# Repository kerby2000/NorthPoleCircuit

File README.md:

# North Pole BLE Audio Card

This is a work-in-progress derivative of the original
[Janky Jingle Crew NorthPoleCircuit](https://github.com/Janky-Jingle-Crew/NorthPoleCircuit).

The goal is to turn the original moving magnetic Christmas PCB card into a BLE-enabled audio postcard / mini-diorama with rechargeable battery power, real audio playback, capacitive touch controls, Hall checkpoints, and addressable RGB lighting.

## Status

Current state: hardware revision in progress.

- KiCad 10 PCB project is included under `PCB/`.
- Draft JLCPCB manufacturing files are included under `PCB/production/`.
- Firmware bring-up scaffold lives under `Firmware/northpole_ch592_bringup/` and is based on the WCH CH592 EVT BLE Peripheral project.
- The board has not yet been validated on real hardware.
- The audio playback IC sourcing is still a risk and should be checked before ordering.

Do not treat the current production files as a proven release. Review ERC/DRC, BOM sourcing, assembly rotations, antenna keepout, LiPo safety, and audio availability before manufacturing.

## Repository Layout

```text
PCB/                     KiCad 10 hardware project and draft manufacturing files
Firmware/                CH592X BLE/audio firmware bring-up project and docs
audio_assets/            WT2003 external-flash manifest and copy-order packer
Code/                    Original upstream firmware, kept for reference only
CAD/                     Original upstream mechanical assets
Media/                   Original media plus new PCB renders
CHANGES_FROM_ORIGINAL.md Summary of the redesign
```

## Hardware Overview

This redesign keeps the magnetic track idea from the original project, but changes most of the control electronics.

Main blocks in the current KiCad design:

- CH592X BLE MCU
- 3 x DRV8837 H-bridge motor drivers
- WT2003H4-24SS audio playback IC
- PY25Q64HA SPI NOR flash for audio assets
- IP5209 1S LiPo charge / boost PMIC
- ME6211 3.3 V regulator
- 2 x DRV5032 Hall sensors
- 4 capacitive touch buttons
- 6 x 1010 addressable RGB LEDs, currently JLCPCB `C41347988`
- USB-C input
- 32 MHz crystal
- WCH-style PCB BLE antenna footprint
- J3 WCH-LinkE/debug Tag-Connect footprint
- J4 WT2003 USB update Tag-Connect footprint
- thin speaker and 1S LiPo battery placement helpers

## Opening The PCB

Use KiCad 10.

Open:

```text
PCB/NorthPoleCircuit_PCB.kicad_pro
```

The local custom libraries are kept in the repo:

- `PCB/cust_sym.kicad_sym`
- `PCB/cust_fp/`
- `PCB/footprints.pretty/`

## Manufacturing Files

Draft manufacturing outputs are in:

```text
PCB/production/
```

Included files:

- `NorthPoleCircuit_PCB14.zip` - Gerber/drill archive
- `bom.csv` - JLCPCB BOM
- `positions.csv` - JLCPCB pick-and-place
- `designators.csv` - Fabrication Toolkit designator output

Before ordering, re-export these from KiCad/Fabrication Toolkit and compare against the files here.

## Firmware

Firmware for this revision is under [Firmware/](./Firmware/). The initial target is `Firmware/northpole_ch592_bringup/`, copied from a working WCH CH592 EVT BLE Peripheral example and then modified at the application layer.

Important hardware notes:

- J3 is WCH-LinkE/debug: 1=3.3V target reference, 2=TIO/SWDIO/PB14, 4=TCK/SWDCK/PB15, 5=GND, 3/6=NC.
- PB14/PB15 are shared with IP5209 I2C through R15/R14 0 ohm links. Do not expect IP5209 I2C access during active WCH-LinkE debugging.
- J4 is intended as WT2003 USB update only, not ARM SWD, but the current PCB revision is blocked for update use: pin 1 is unconnected, so J4 has D+/D-/GND only. Do not use it for WT2003 USB update until +5 V is routed or a rework power path is documented.
- PB0 controls global DRV8837 `~SLEEP`; idle/fault state is `/SLEEP` low and all bridge IN pins low.

The existing `Code/` directory is from the original upstream NorthPoleCircuit project and is not firmware for the CH592X BLE/audio redesign.

## Major Changes

See [CHANGES_FROM_ORIGINAL.md](./CHANGES_FROM_ORIGINAL.md).

Short version:

- single BLE-capable CH592X control architecture
- rechargeable LiPo power path
- audio playback IC and speaker path
- capacitive touch buttons
- Hall checkpoint sensing
- addressable RGB LEDs
- revised KiCad 10 PCB with custom artwork and JLCPCB metadata

## Attribution

Original project:

- [Janky Jingle Crew - NorthPoleCircuit](https://github.com/Janky-Jingle-Crew/NorthPoleCircuit)

Related inspiration:

- [Jeff McBride - Gauss Speedway](https://jeffmcbride.net/gauss-speedway/)

This repository is a derivative redesign. The original concept, mechanical idea, and much of the visual/magnetic-track inspiration belong to the original authors.

## License

TODO.

Before publishing a release or manufacturing publicly, verify the license/permission status of the upstream NorthPoleCircuit project. If the upstream project has no explicit open-source license, only the new original work in this redesign can be licensed without additional permission.

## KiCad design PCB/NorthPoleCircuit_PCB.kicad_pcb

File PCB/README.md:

# PCB

This folder contains the KiCad 10 hardware project for the BLE/audio redesign.

Open `NorthPoleCircuit_PCB.kicad_pro` in KiCad 10.

Local project assets:

- `cust_sym.kicad_sym` - custom symbols
- `cust_fp/` - custom footprints used by the board
- `footprints.pretty/` - local STEP models referenced by the PCB
- `production/` - draft manufacturing outputs

The production files are draft outputs for review. Re-export them from KiCad/Fabrication Toolkit before ordering boards.

## Firmware And Bring-Up

The detailed CH592X firmware implementation and first-board bring-up plan is maintained in `../Firmware/README.md`.

Use the bring-up/test firmware profile first. It should keep all high-power outputs disabled at boot and expose explicit diagnostic hooks for power, touch, RGB LEDs, Hall sensors, audio, BLE, and DRV8837 motor testing before running the production firmware.

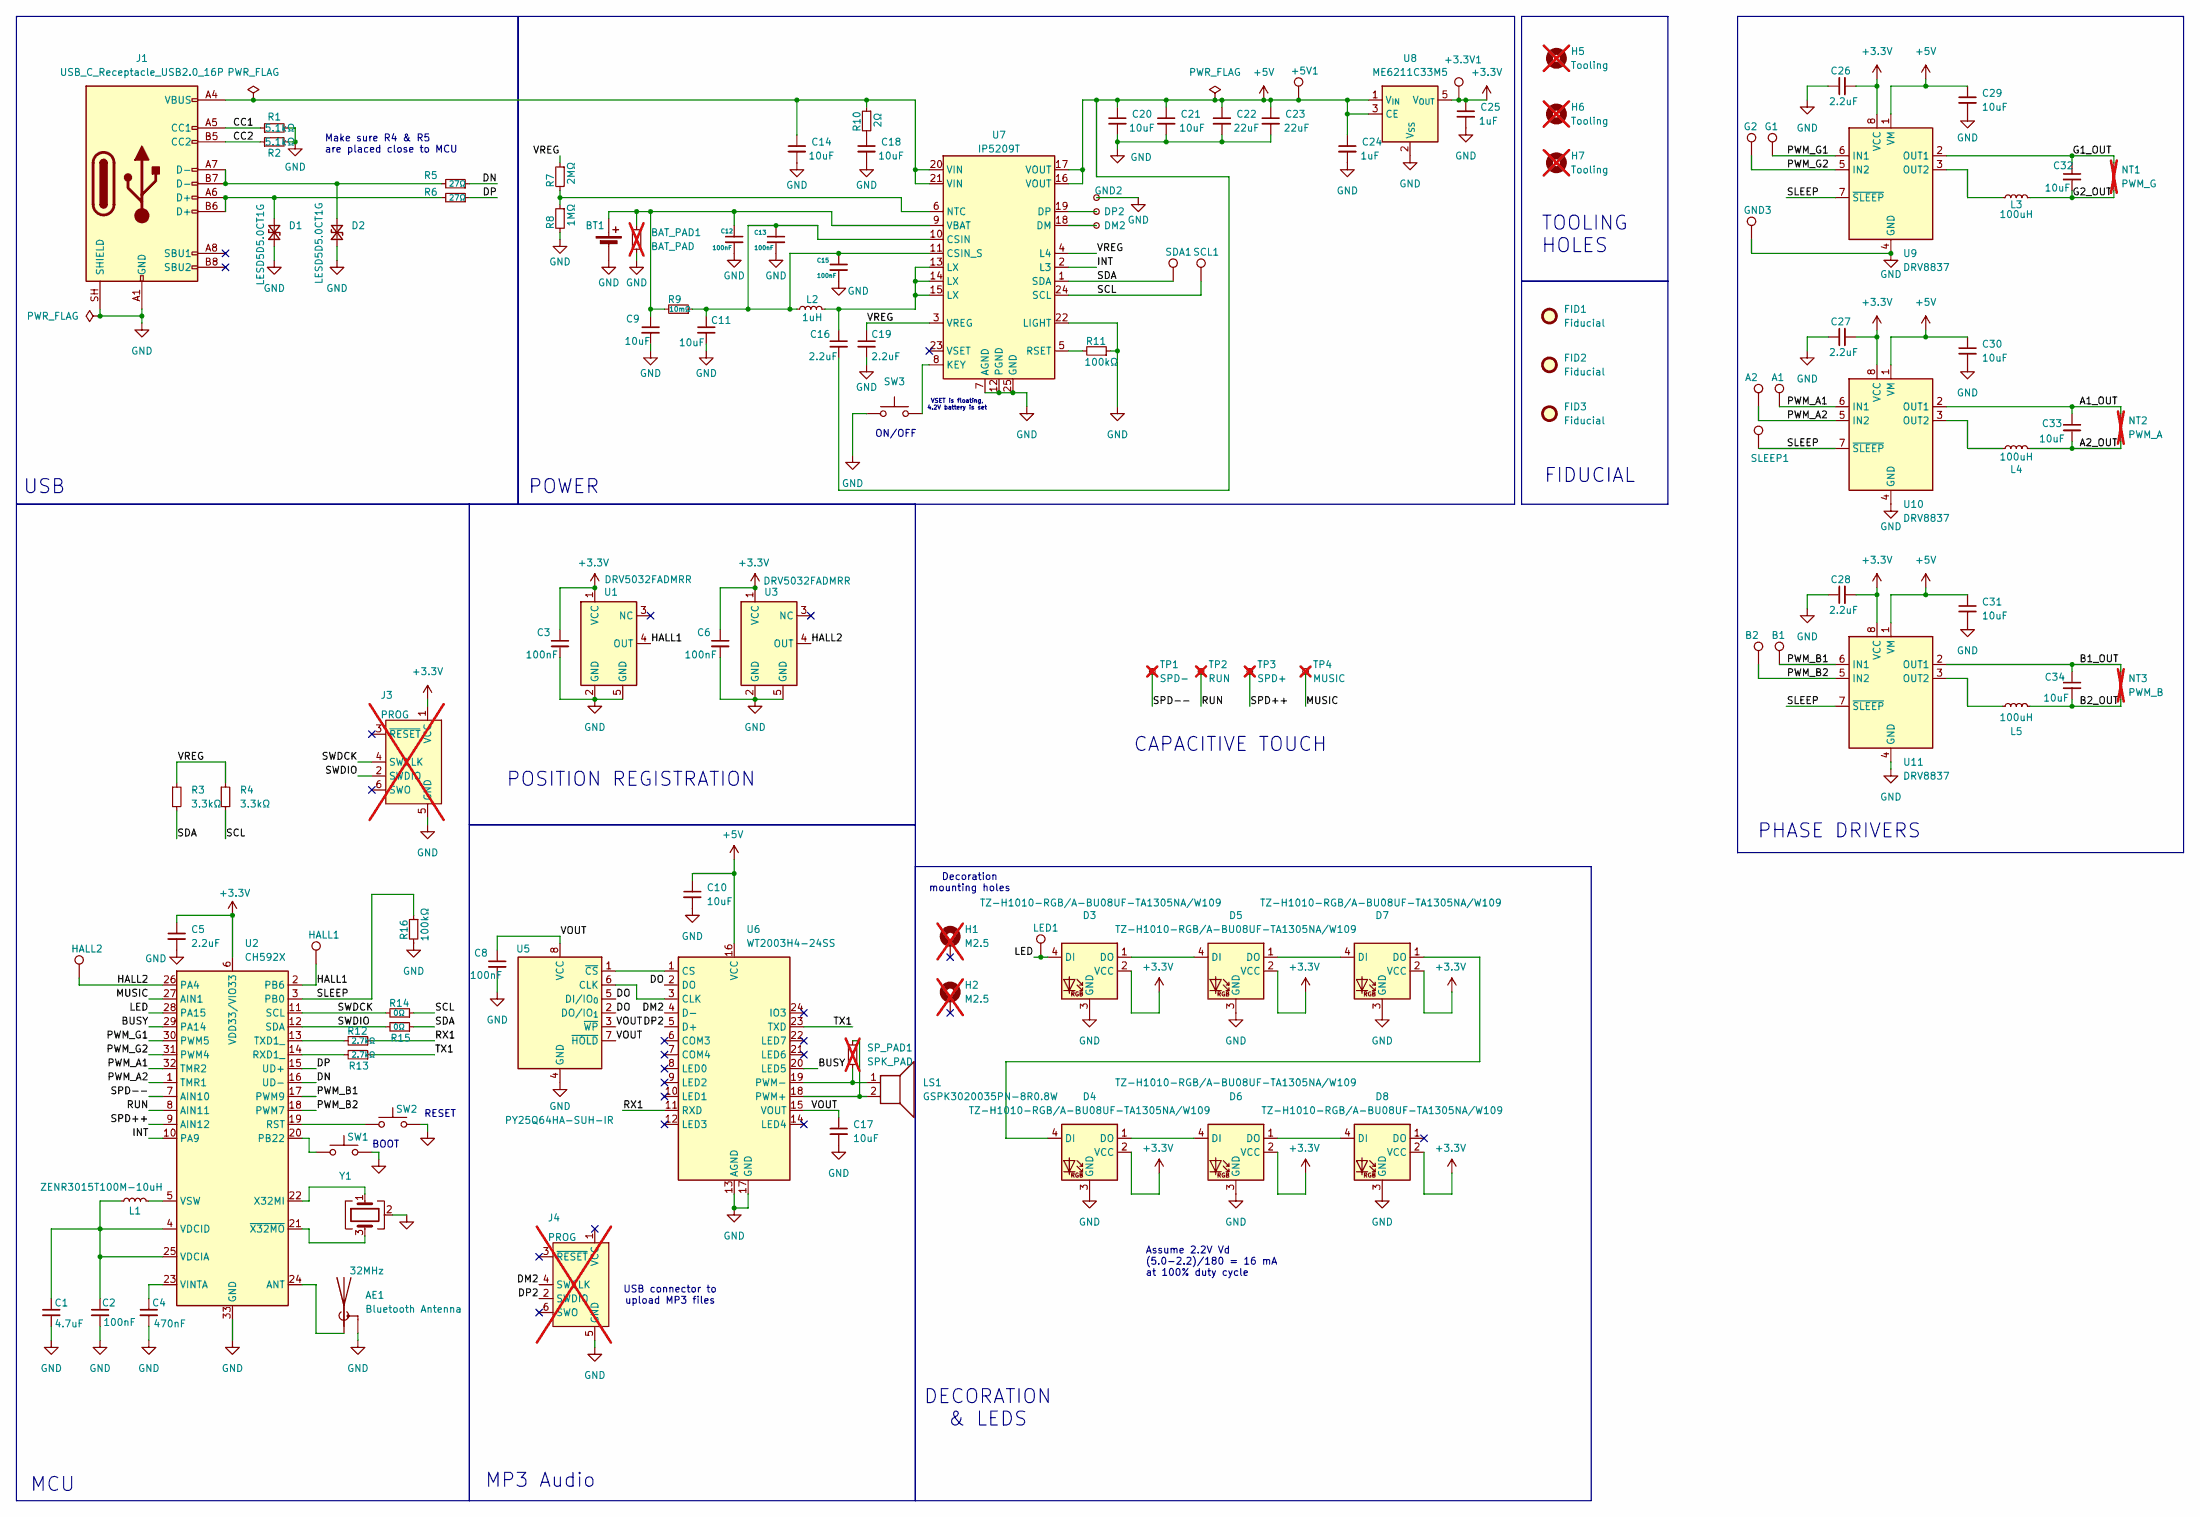
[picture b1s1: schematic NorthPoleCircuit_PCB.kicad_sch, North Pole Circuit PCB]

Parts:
+3.3V1: +3.3V; TestPoint_Pad_D1.5mm
+5V1: +5V; TestPoint_Pad_D1.5mm
A1: A1; TestPoint_Pad_D1.5mm
A2: A2; TestPoint_Pad_D1.5mm
AE1: Bluetooth Antenna; WCH_ANT_F_1_2_4G_1p0mmFR4_12p3x5p6
B1: B1; TestPoint_Pad_D1.5mm
B2: B2; TestPoint_Pad_D1.5mm
BAT_PAD1: BAT_PAD; Battery_LiPo_500mAh_30x35x4mm_WirePads; not fitted
BT1: LiPo_1S_500mAh; Battery_LiPo_500mAh_30x35x4mm_Body
C1: 4.7uF; C_1206_3216Metric; MPN CL31B475KAHNNNE; JLCPCB C1872
C2, C3, C6, C8, C12, C13, C15: 100nF; C_0402_1005Metric; MPN CL05B104KO5NNNC; JLCPCB C1525
C4: 470nF; C_1206_3216Metric; MPN CL31B474KBHNNNE; JLCPCB C71084
C5, C16, C19, C26, C27, C28: 2.2uF; C_1206_3216Metric; MPN CL31B225KBHNNNE; JLCPCB C50254
C9, C10, C11, C14, C17, C18, C20, C21, C29, C30, C31, C32, C33, C34: 10uF; C_1206_3216Metric; MPN CL31A106KBHNNNE; JLCPCB C13585
C22, C23: 22uF; C_1206_3216Metric; MPN CL31A226KAHNNNE; JLCPCB C12891
C24, C25: 1uF; C_1206_3216Metric; MPN CL31B105KBHNNNE; JLCPCB C1848
D1, D2: LESD5D5.0CT1G; D_SOD-523; MPN LESD5D5.0CT1G(UMW); JLCPCB C5199850
D3, D4, D5, D6, D7, D8: TZ-H1010-RGB/A-BU08UF-TA1305NA/W109; ws2812b_1010; MPN TZ-H1010-RGB/A-BU08UF-TA1305NA/W109; JLCPCB C41347988
DM2: TestPoint_Small; TestPoint_Pad_D1.0mm
DP2: TestPoint_Small; TestPoint_Pad_D1.0mm
FID1, FID2, FID3: Fiducial; Fiducial_0.75mm_Mask1.5mm
G1: G1; TestPoint_Pad_D1.5mm
G2: G2; TestPoint_Pad_D1.5mm
GND2: TestPoint_Small; TestPoint_Pad_D1.0mm
GND3: HALL2; TestPoint_Pad_D1.5mm
H1, H2: M2.5; MountingHole_2.7mm_M2.5_DIN965_Pad; not fitted
H5, H6, H7: Tooling; tooling_hole; not fitted
HALL1: HALL1; TestPoint_Pad_D1.5mm
HALL2: HALL2; TestPoint_Pad_D1.5mm
J1: USB_C_Receptacle_USB2.0_16P; USB_C_Receptacle_HRO_TYPE-C-31-M-12; MPN TYPE-C-31-M-12; JLCPCB C165948
J3, J4: PROG; Tag-Connect_TC2030-IDC-NL_2x03_P1.27mm_Vertical; not fitted
L1: ZENR3015T100M-10uH; L_Taiyo-Yuden_NR-30xx; MPN ZENR3015T100M-10uH; JLCPCB C42427989
L2: 1uH; L_Wuerth_HCI-7030; MPN MAPM0630F-1R0M-LF; JLCPCB C280920
L3, L4, L5: 100uH; SMMS0650-101M; MPN SMMS0650-101M; JLCPCB C2894722
LED1: LED; TestPoint_Pad_D1.5mm
LS1: GSPK3020035PN-8R0.8W
NT1: PWM_G; NetTie_1.25mm; not fitted
NT2: PWM_A; NetTie_1.25mm; not fitted
NT3: PWM_B; NetTie_1.25mm; not fitted
R1, R2: 5.1kΩ; R_0402_1005Metric; MPN 0402WGF5101TCE; JLCPCB C25905
R3, R4: 3.3kΩ; R_0402_1005Metric; MPN 0402WGF3301TCE; JLCPCB PN C25890
R5, R6: 27Ω; R_0402_1005Metric; MPN 0402WGF270JTCE; JLCPCB C25100
R7: 2MΩ; R_0805_2012Metric; MPN 0805W8J0205T5E; JLCPCB C40088
R8: 1MΩ; R_0402_1005Metric; MPN 0402WGF1004TCE; JLCPCB C26083
R9: 10mΩ; R_1206_3216Metric; MPN FRM121WFR010TM; JLCPCB C7467248
R10: 2Ω; R_0402_1005Metric; MPN 0402WGJ020JTCE; JLCPCB C25157
R11, R16: 100kΩ; R_0402_1005Metric; MPN 0402WGF1003TCE; JLCPCB C25741
R12, R13: 2.7kΩ; R_0402_1005Metric; MFR.Part # 0402WGF2701TCE; LCSC Part C25885
R14, R15: 0Ω; R_0402_1005Metric; MFR.Part # 0402WGF0000TCE; LCSC Part C17168
SCL1: SCL; TestPoint_Pad_D1.5mm
SDA1: SDA; TestPoint_Pad_D1.5mm
SLEEP1: SLEEP; TestPoint_Pad_D1.5mm
SP_PAD1: SPK_PAD; Speaker_GSPK3020035PN_WirePads; not fitted
SW1, SW2: TS-1088-AR02016; SW_Push_SPST_NO_Alps_SKRK; MPN TS-1088-AR02016; JLCPCB C720477
SW3: TS-1187A-C-E-B; SW_SPST_SKQG_WithStem; MPN TS-1187A-C-E-B; JLCPCB C318887
TP1: SPD-; Cap_Touch_10mm; not fitted
TP2: RUN; Cap_Touch_10mm; not fitted
TP3: SPD+; Cap_Touch_10mm; not fitted
TP4: MUSIC; Cap_Touch_10mm; not fitted
U1, U3: DRV5032FADMRR; Texas_X2SON-4-1EP_1.1x1.4mm_P0.5mm_EP0.8x0.6mm; MPN DRV5032FADMRR; JLCPCB C2152496
U2: CH592X; QFN-32-1EP_4x4mm_P0.4mm_EP2.65x2.65mm; MPN CH592X; JLCPCB C42442063
U5: PY25Q64HA-SUH-IR; SOIC-8_5.3x5.3mm_P1.27mm; MPN PY25Q64HA-SUH-IR; JLCPCB C22438999
U6: WT2003H4-24SS; SSOP-24_3.9x8.7mm_P0.635mm; MPN WT2003H4-24SS; JLCPCB C2931181
U7: IP5209T; QFN-24-1EP_4x4mm_P0.5mm_EP2.5x2.5mm; MPN IP5209T; JLCPCB C284964
U8: ME6211C33M5; SOT-23-5; MPN ME6211C33M5G-N; JLCPCB C82942
U9, U10, U11: DRV8837; WSON-8-1EP_2x2mm_P0.5mm_EP0.9x1.6mm; MPN DRV8837DSGR; JLCPCB C39159
Y1: 32MHz; Crystal_SMD_3225-4Pin_3.2x2.5mm; MPN X322532MOB4SI; LCSC Part C9009

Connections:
+3.3V: +3.3V1.1 (1_1), C3.1, C5.1, C6.1, C25.1, C26.2, C27.2, C28.2, D3.2 (VCC), D4.2 (VCC), D5.2 (VCC), D6.2 (VCC), D7.2 (VCC), D8.2 (VCC), J3.1 (VCC), U1.1 (VCC), U2.6 (VDD33/VIO33), U3.1 (VCC), U8.5 (V_{OUT}), U9.8 (VCC), U10.8 (VCC), U11.8 (VCC)
+5V: +5V1.1 (1_1), C10.1, C16.2, C20.1, C21.1, C22.1, C23.1, C24.1, C29.1, C30.1, C31.1, U6.16 (VCC), U7.16 (VOUT), U7.17 (VOUT), U8.1 (V_{IN}), U8.3 (CE), U9.1 (VM), U10.1 (VM), U11.1 (VM)
/A1_OUT: C33.1, NT2.2, U10.2 (OUT1)
/A2_OUT: C33.2, L4.2, NT2.1
/B1_OUT: C34.1, NT3.2, U11.2 (OUT1)
/B2_OUT: C34.2, L5.2, NT3.1
/BUSY: U2.29 (PA14), U6.20 (LED5)
/CC1: J1.A5 (CC1), R1.1
/CC2: J1.B5 (CC2), R2.1
/DM2: J4.4 (SWCLK), U6.4 (D-)
/DN: R5.1, U2.16 (UD-)
/DO: U5.2 (DO/IO_{1}), U5.5 (DI/IO_{0}), U6.2 (DO)
/DP: R6.1, U2.15 (UD+)
/DP2: J4.2 (SWDIO), U6.5 (D+)
/G1_OUT: C32.1, NT1.2, U9.2 (OUT1)
/G2_OUT: C32.2, L3.2, NT1.1
/INT: U2.10 (PA9), U7.2 (L3)
/LED: D3.4 (DI), LED1.1 (1_1), U2.28 (PA15)
/MUSIC: TP4.1 (1_1), U2.27 (AIN1)
/PWM_A1: A1.1 (1_1), U2.32 (TMR2), U10.6 (IN1)
/PWM_A2: A2.1 (1_1), U2.1 (TMR1), U10.5 (IN2)
/PWM_B1: B1.1 (1_1), U2.17 (PWM9), U11.6 (IN1)
/PWM_B2: B2.1 (1_1), U2.18 (PWM7), U11.5 (IN2)
/PWM_G1: G1.1 (1_1), U2.30 (PWM5), U9.6 (IN1)
/PWM_G2: G2.1 (1_1), U2.31 (PWM4), U9.5 (IN2)
/RUN: TP2.1 (1_1), U2.8 (AIN11)
/RX1: R12.1, U6.11 (RXD)
/SCL: R4.2, R14.1, SCL1.1 (1_1), U7.24 (SCL)
/SDA: R3.2, R15.1, SDA1.1 (1_1), U7.1 (SDA)
/SLEEP: R16.1, SLEEP1.1 (1_1), U2.3 (PB0), U9.7 (~SLEEP), U10.7 (~SLEEP), U11.7 (~SLEEP)
/SPD++: TP3.1 (1_1), U2.9 (AIN12)
/SPD--: TP1.1 (1_1), U2.7 (AIN10)
/SWDCK: J3.4 (SWCLK), R14.2, U2.11 (SCL)
/SWDIO: J3.2 (SWDIO), R15.2, U2.12 (SDA)
/TX1: R13.1, U6.23 (TXD)
/VOUT: C8.1, C17.1, U5.3 (~WP), U5.7 (~HOLD), U5.8 (VCC), U6.15 (VOUT)
/VREG: C19.1, R3.1, R4.1, R7.1, U7.3 (VREG), U7.4 (L4)
unnamed: AE1.1 (A), U2.24 (ANT)
unnamed: C14.1, J1.A4 (VBUS), J1.A9 (VBUS), J1.B4 (VBUS), J1.B9 (VBUS), R10.1, U7.20 (VIN), U7.21 (VIN)
unnamed: C16.1, L2.2, U7.13 (LX), U7.14 (LX), U7.15 (LX)
unnamed: C18.1, R10.2
unnamed: D1.2 (A2), J1.A6 (D+), J1.B6 (D+), R6.2
unnamed: D2.2 (A2), J1.A7 (D-), J1.B7 (D-), R5.2
unnamed: D3.1 (DO), D5.4 (DI)
unnamed: D4.4 (DI), D7.1 (DO)
unnamed: D4.1 (DO), D6.4 (DI)
unnamed: D5.1 (DO), D7.4 (DI)
unnamed: D6.1 (DO), D8.4 (DI)
unnamed: R13.2, U2.14 (RXD1_)
unnamed: R12.2, U2.13 (TXD1_)
unnamed: SW1.1, U2.20 (PB22)
unnamed: SW2.1, U2.19 (RST)
unnamed: C1.1, C2.1, L1.1, U2.4 (VDCID), U2.25 (VDCIA)
unnamed: C4.1, U2.23 (VINTA)
unnamed: L1.2, U2.5 (VSW)
unnamed: U2.22 (X32MI), Y1.1
unnamed: U2.21 (~X32MO), Y1.3
unnamed: U5.6 (CLK), U6.3 (CLK)
unnamed: U5.1 (~CS), U6.1 (CS)
unnamed: LS1.2, SP_PAD1.1, U6.18 (PWM+)
unnamed: LS1.1, SP_PAD1.2, U6.19 (PWM-)
unnamed: C11.1, C13.1, C15.1, L2.1, R9.1, U7.10 (CSIN), U7.11 (CSIN_S)
unnamed: DM2.1 (1_1), U7.18 (DM)
unnamed: DP2.1 (1_1), U7.19 (DP)
unnamed: SW3.2, U7.8 (KEY)
unnamed: R7.2, R8.1, U7.6 (NTC)
unnamed: R11.2, U7.5 (RSET)
unnamed: BAT_PAD1.1, BT1.1 (+), C9.1, C12.1, R9.2, U7.9 (VBAT)
unnamed: L3.1, U9.3 (OUT2)
unnamed: L4.1, U10.3 (OUT2)
unnamed: L5.1, U11.3 (OUT2)

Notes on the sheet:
MCU
RESET
DECORATION & LEDS
USB
POWER
FIDUCIAL
CAPACITIVE TOUCH
USB connector to upload MP3 files
POSITION REGISTRATION
ON/OFF
Decoration mounting holes
TOOLING HOLES
MP3 Audio
Assume 2.2V Vd (5.0-2.2)/180 = 16 mA at 100% duty cycle
Make sure R4 & R5 are placed close to MCU
BOOT
PHASE DRIVERS
VSET is floating, 4.2V battery is set

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
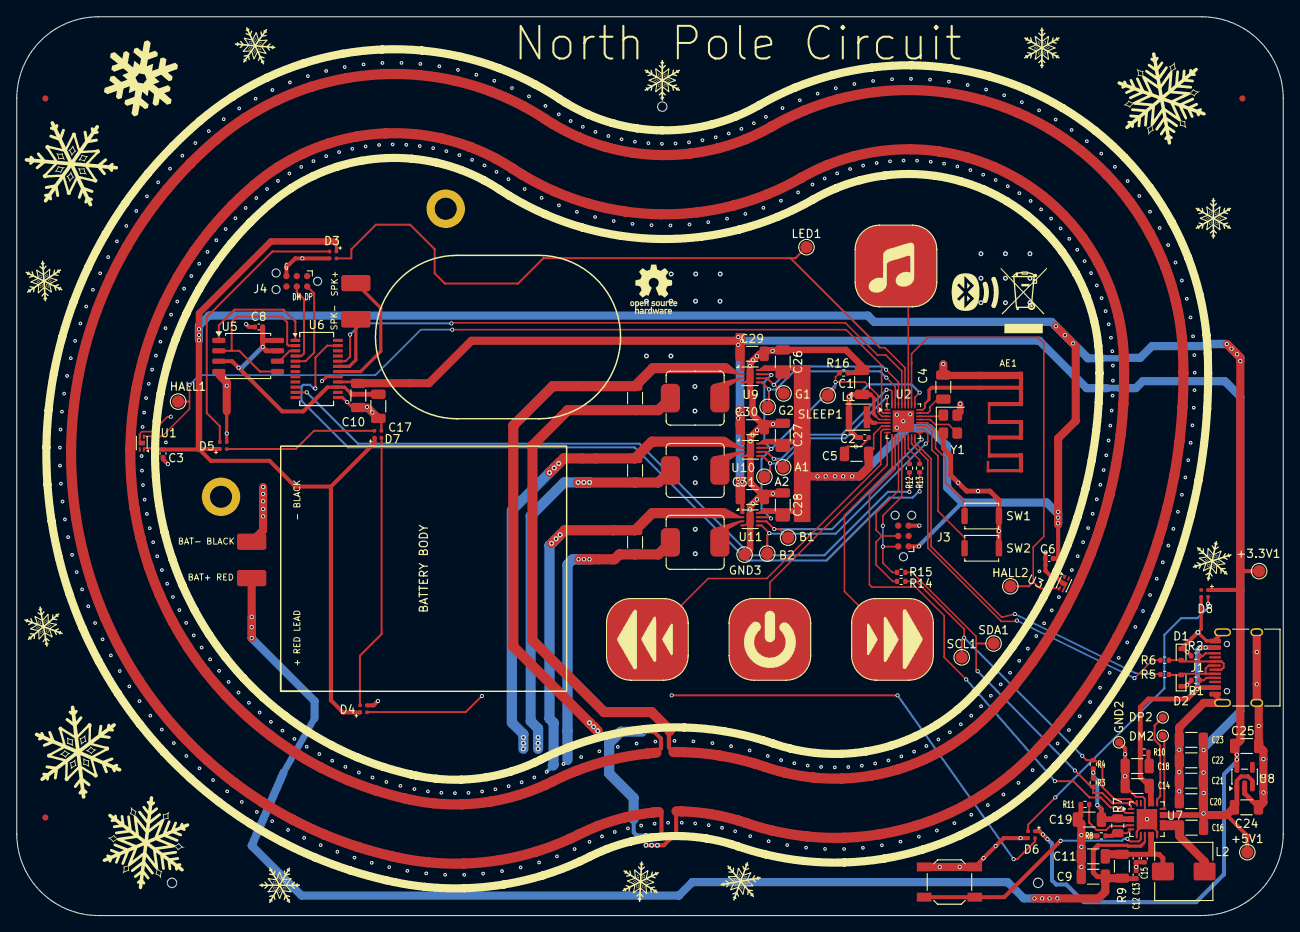
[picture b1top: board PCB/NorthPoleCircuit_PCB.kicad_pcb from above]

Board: 4 copper layers, 155.0 x 110.0 mm, 117 parts (0 on the bottom side), 74 nets.

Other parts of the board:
BT1_BODY: LiPo_1S_500mAh; Battery_LiPo_500mAh_30x35x4mm_Body
LS1_BODY: GSPK3020035PN-8R0.8W; Speaker_GSPK3020035PN_Body

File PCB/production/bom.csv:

Designator,Footprint,Quantity,Value,LCSC Part #,JLCPCB Part #,JLCPCB,MPN,MFR.Part #
C1,1206,1,4.7uF,C1872,C1872,C1872,CL31B475KAHNNNE,
"C10, C11, C14, C17, C18, C20, C21, C29, C30, C31, C32, C33, C34, C9",1206,14,10uF,C13585,C13585,C13585,CL31A106KBHNNNE,
"C12, C13, C15, C2, C3, C6, C8",0402,7,100nF,C1525,C1525,C1525,CL05B104KO5NNNC,
"C16, C19, C26, C27, C28, C5",1206,6,2.2uF,C50254,C50254,C50254,CL31B225KBHNNNE,
"C22, C23",1206,2,22uF,C12891,C12891,C12891,CL31A226KAHNNNE,
"C24, C25",1206,2,1uF,C1848,C1848,C1848,CL31B105KBHNNNE,
C4,1206,1,470nF,C71084,C71084,C71084,CL31B474KBHNNNE,
"D1, D2",D_SOD-523,2,LESD5D5.0CT1G,C5199850,C5199850,C5199850,LESD5D5.0CT1G(UMW),
"D3, D4, D5, D6, D7, D8",ws2812b_1010,6,TZ-H1010-RGB/A-BU08UF-TA1305NA/W109,C41347988,C41347988,C41347988,TZ-H1010-RGB/A-BU08UF-TA1305NA/W109,TZ-H1010-RGB/A-BU08UF-TA1305NA/W109
J1,USB_C_Receptacle_HRO_TYPE-C-31-M-12,1,USB_C_Receptacle_USB2.0_16P,C165948,C165948,C165948,TYPE-C-31-M-12,
L1,L_Taiyo-Yuden_NR-30xx,1,ZENR3015T100M-10uH,C42427989,C42427989,C42427989,ZENR3015T100M-10uH,
L2,L_Wuerth_HCI-7030,1,1uH,C280920,C280920,C280920,MAPM0630F-1R0M-LF,
"L3, L4, L5",SMMS0650-101M,3,100uH,C2894722,C2894722,C2894722,SMMS0650-101M,
"R1, R2",0402,2,5.1kΩ,C25905,C25905,C25905,0402WGF5101TCE,
R10,0402,1,2Ω,C25157,C25157,C25157,0402WGJ020JTCE,
R11,0402,1,100kΩ,C25741,C25741,C25741,0402WGF1003TCE,
"R12, R13",0402,2,2.7kΩ,C25885,C25885,C25885,0402WGF2701TCE,0402WGF2701TCE
"R3, R4",0402,2,3.3kΩ,C25890,C25890,C25890,0402WGF3301TCE,
"R5, R6",0402,2,27Ω,C25100,C25100,C25100,0402WGF270JTCE,
R7,0805,1,2MΩ,C40088,C40088,C40088,0805W8J0205T5E,
R8,0402,1,1MΩ,C26083,C26083,C26083,0402WGF1004TCE,
R9,1206,1,10mΩ,C7467248,C7467248,C7467248,FRM121WFR010TM,
"SW1, SW2",SW_Push_SPST_NO_Alps_SKRK,2,TS-1088-AR02016,C720477,C720477,C720477,TS-1088-AR02016,
SW3,SW_SPST_SKQG_WithStem,1,TS-1187A-C-E-B,C318887,C318887,C318887,TS-1187A-C-E-B,
"U1, U3",Texas_X2SON-4-1EP_1.1x1.4mm_P0.5mm_EP0.8x0.6mm,2,DRV5032FADMRR,C2152496,C2152496,C2152496,DRV5032FADMRR,
"U10, U11, U9",WSON-8-1EP_2x2mm_P0.5mm_EP0.9x1.6mm,3,DRV8837,C39159,C39159,C39159,DRV8837DSGR,
U2,QFN-32-1EP_4x4mm_P0.4mm_EP2.65x2.65mm,1,CH592X,C42442063,C42442063,C42442063,CH592X,
U5,SOIC-8_5.3x5.3mm_P1.27mm,1,PY25Q64HA-SUH-IR,C22438999,C22438999,C22438999,PY25Q64HA-SUH-IR,
U6,SSOP-24_3.9x8.7mm_P0.635mm,1,WT2003H4-24SS,C2931181,C2931181,C2931181,WT2003H4-24SS,
U7,QFN-24-1EP_4x4mm_P0.5mm_EP2.5x2.5mm,1,IP5209T,C284964,C284964,C284964,IP5209T,
U8,SOT-23-5,1,ME6211C33M5,C82942,C82942,C82942,ME6211C33M5G-N,
Y1,Crystal_SMD_3225-4Pin_3.2x2.5mm,1,32MHz,C9009,C9009,C9009,X322532MOB4SI,

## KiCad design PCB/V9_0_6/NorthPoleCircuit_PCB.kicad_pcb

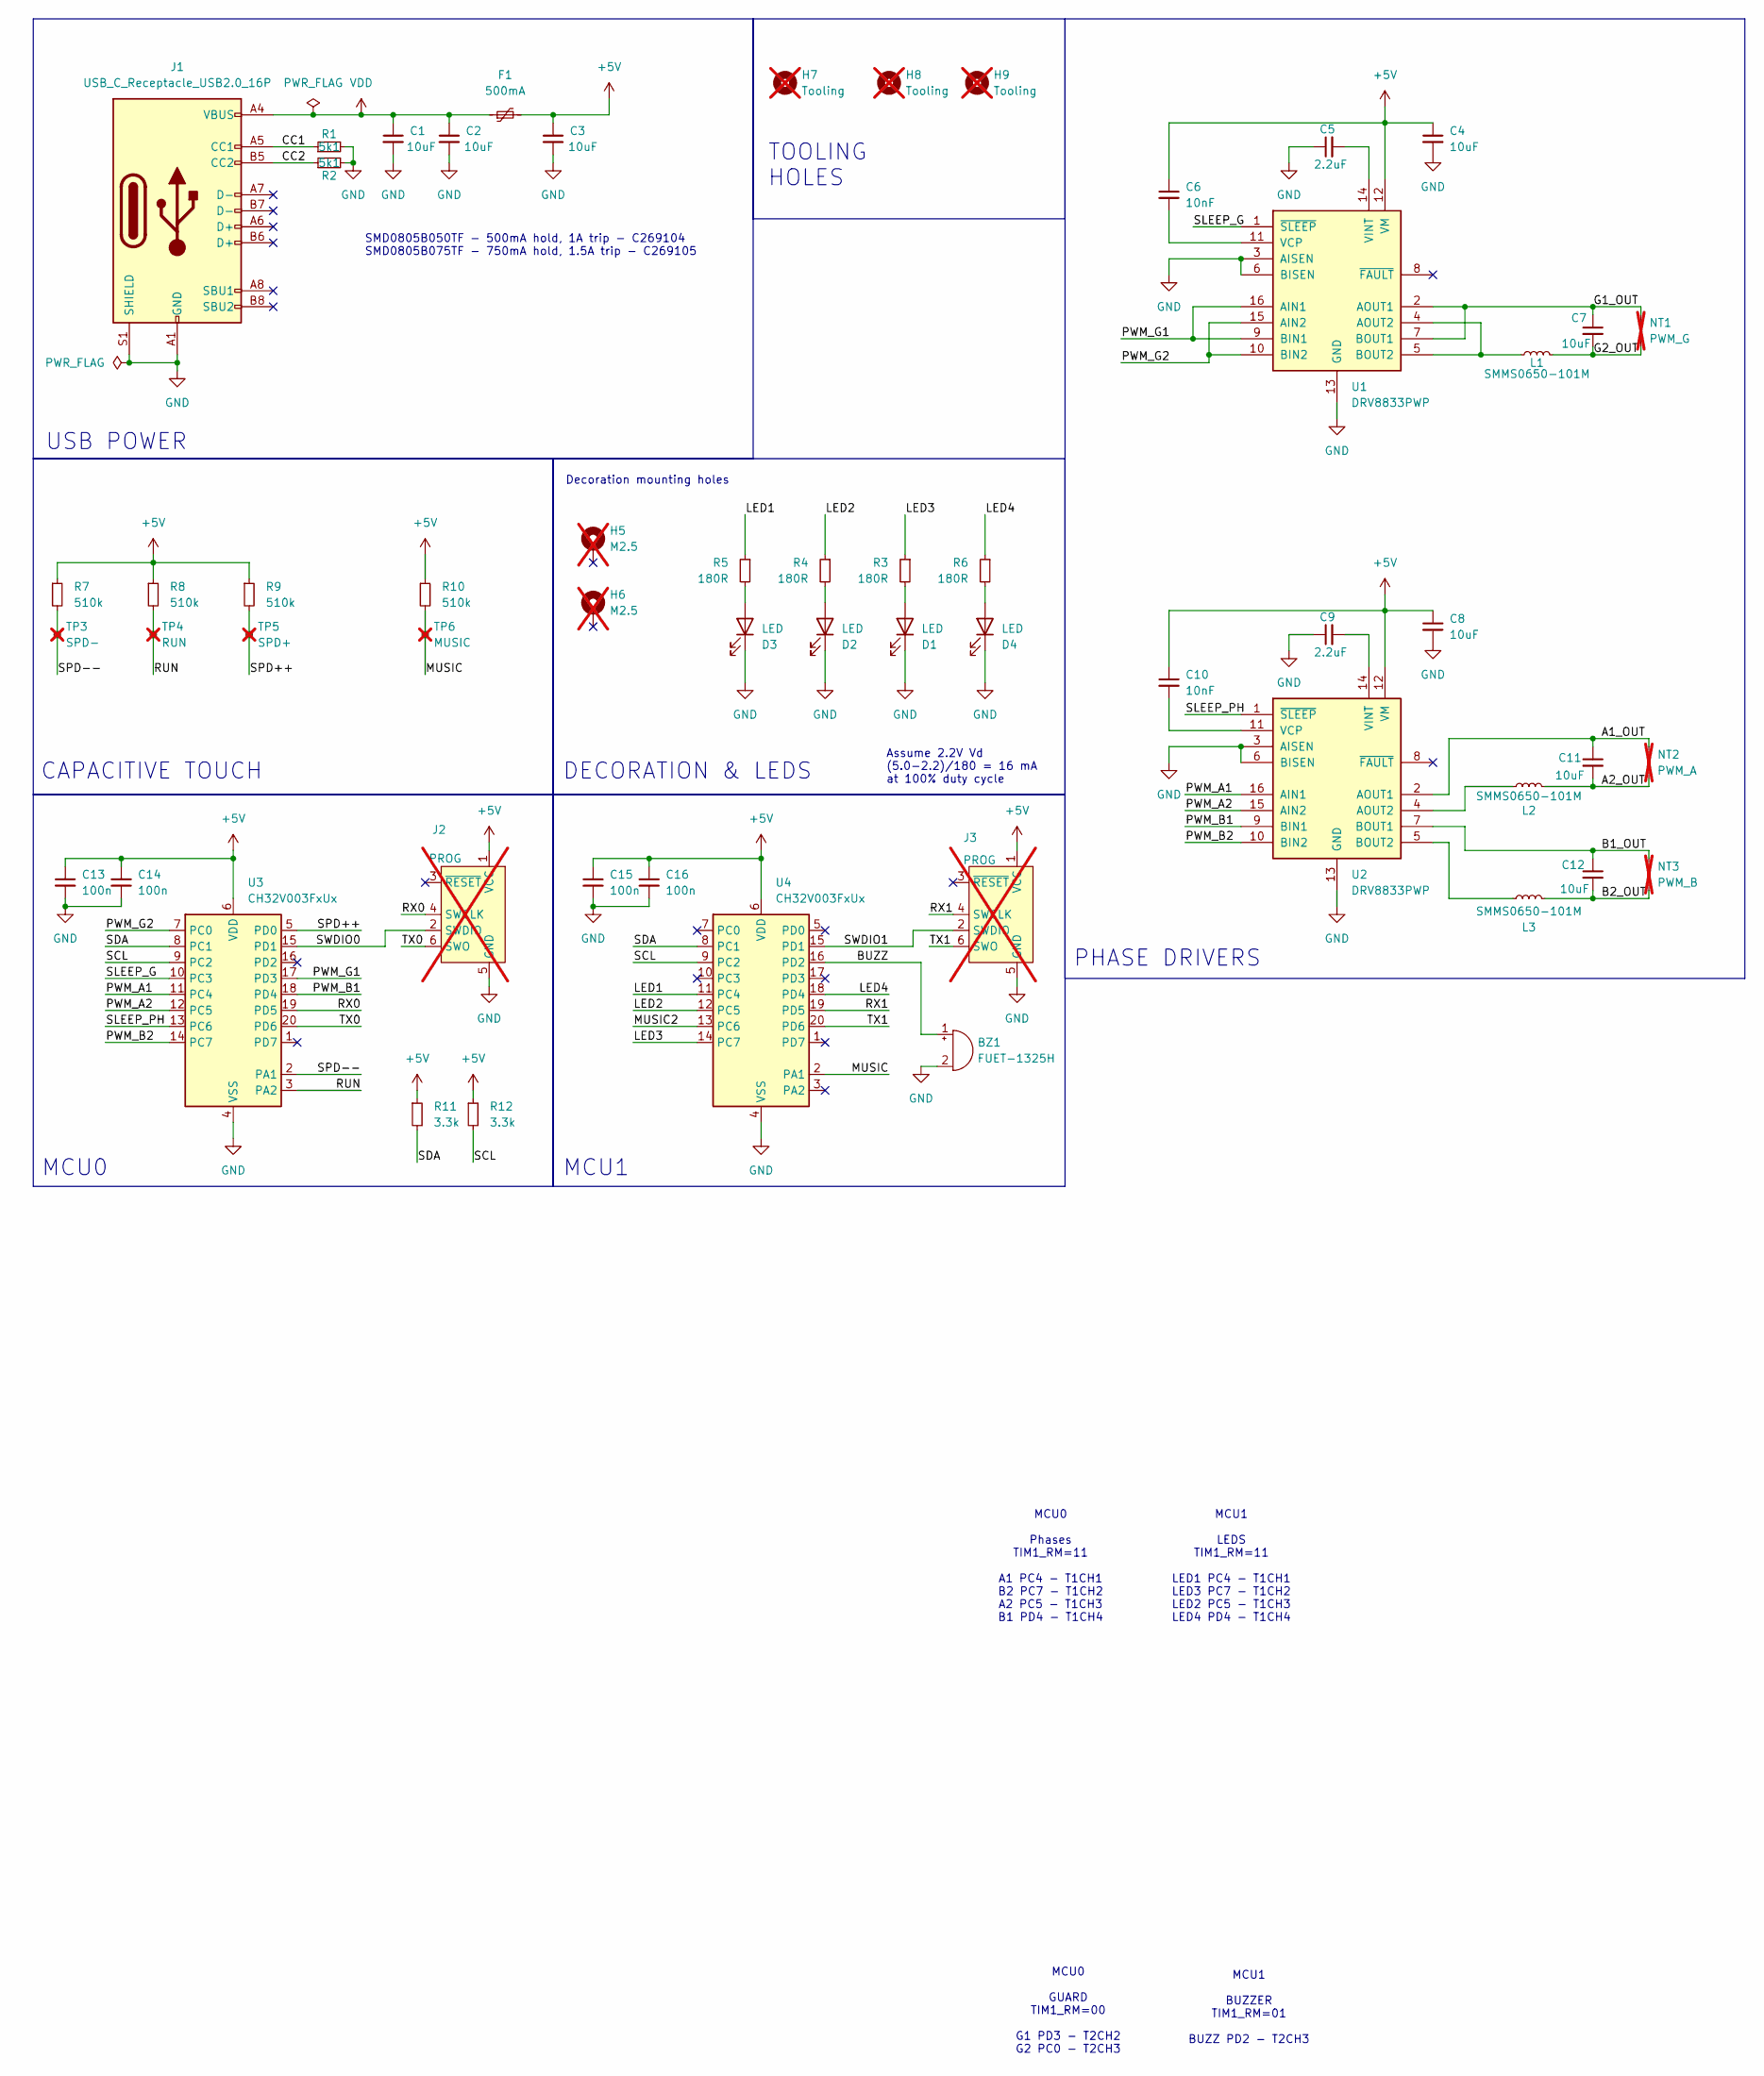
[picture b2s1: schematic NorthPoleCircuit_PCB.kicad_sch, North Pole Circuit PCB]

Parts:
BZ1: FUET-1325H; FUET-1325; MPN C2982583
C1, C2, C3, C4, C7, C8, C11, C12: 10uF; C_1206_3216Metric; MPN C13585
C5, C9: 2.2uF; C_1206_3216Metric; MPN C50254
C6, C10: 10nF; C_0402_1005Metric; MPN C15195
C13, C14, C15, C16: 100n; C_0402_1005Metric; MPN C1525
D1, D2, D3, D4: LED; LED_0805_2012Metric; MPN C5878906
F1: 500mA; Fuse_0805_2012Metric; MPN C269104
H5, H6: M2.5; MountingHole_2.7mm_M2.5_DIN965_Pad; not fitted
H7, H8, H9: Tooling; tooling_hole; not fitted
J1: USB_C_Receptacle_USB2.0_16P; USB_C_Receptacle_HRO_TYPE-C-31-M-12; MPN C165948
J2, J3: PROG; Tag-Connect_TC2030-IDC-NL_2x03_P1.27mm_Vertical; not fitted
L1, L2, L3: SMMS0650-101M; MPN C2894722
NT1: PWM_G; NetTie_1.25mm; not fitted
NT2: PWM_A; NetTie_1.25mm; not fitted
NT3: PWM_B; NetTie_1.25mm; not fitted
R1, R2: 5k1; R_0603_1608Metric; MPN C23186
R3, R4, R5, R6: 180R; R_0805_2012Metric; MPN C25270
R7, R8, R9, R10: 510k; R_0603_1608Metric; MPN C23192
R11, R12: 3.3k; R_0402_1005Metric; MPN C25890
TP3: SPD-; Cap_Touch_10mm; not fitted
TP4: RUN; Cap_Touch_10mm; not fitted
TP5: SPD+; Cap_Touch_10mm; not fitted
TP6: MUSIC; Cap_Touch_10mm; not fitted
U1, U2: DRV8833PWP; HTSSOP-16-1EP_4.4x5mm_P0.65mm_EP3.4x5mm_Mask2.46x2.31mm_The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; MPN C50506
U3, U4: CH32V003FxUx; QFN-20-1EP_3x3mm_P0.4mm_EP1.65x1.65mm; MPN C5299908

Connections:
+5V: C3.1, C4.1, C6.1, C8.1, C10.1, C13.1, C14.1, C15.1, C16.1, F1.2, J2.1 (VCC), J3.1 (VCC), R7.1, R8.1, R9.1, R10.1, R11.1, R12.1, U1.12 (VM), U2.12 (VM), U3.6 (VDD), U4.6 (VDD)
/A1_OUT: C11.1, NT2.2, U2.2 (AOUT1)
/A2_OUT: C11.2, L2.2, NT2.1
/B1_OUT: C12.1, NT3.2, U2.7 (BOUT1)
/B2_OUT: C12.2, L3.2, NT3.1
/BUZZ: BZ1.1 (+), U4.16 (PD2)
/CC1: J1.A5 (CC1), R1.1
/CC2: J1.B5 (CC2), R2.1
/G1_OUT: C7.1, NT1.2, U1.2 (AOUT1), U1.7 (BOUT1)
/G2_OUT: C7.2, L1.2, NT1.1
/LED1: R5.1, U4.11 (PC4)
/LED2: R4.1, U4.12 (PC5)
/LED3: R3.1, U4.14 (PC7)
/LED4: R6.1, U4.18 (PD4)
/MUSIC: R10.2, TP6.1, U4.2 (PA1)
/MUSIC2: U4.13 (PC6)
/PWM_A1: U2.16 (AIN1), U3.11 (PC4)
/PWM_A2: U2.15 (AIN2), U3.12 (PC5)
/PWM_B1: U2.9 (BIN1), U3.18 (PD4)
/PWM_B2: U2.10 (BIN2), U3.14 (PC7)
/PWM_G1: U1.9 (BIN1), U1.16 (AIN1), U3.17 (PD3)
/PWM_G2: U1.10 (BIN2), U1.15 (AIN2), U3.7 (PC0)
/RUN: R8.2, TP4.1, U3.3 (PA2)
/RX0: J2.4 (SWCLK), U3.19 (PD5)
/RX1: J3.4 (SWCLK), U4.19 (PD5)
/SCL: R12.2, U3.9 (PC2), U4.9 (PC2)
/SDA: R11.2, U3.8 (PC1), U4.8 (PC1)
/SLEEP_G: U1.1 (~SLEEP), U3.10 (PC3)
/SLEEP_PH: U2.1 (~SLEEP), U3.13 (PC6)
/SPD++: R9.2, TP5.1, U3.5 (PD0)
/SPD--: R7.2, TP3.1, U3.2 (PA1)
/SWDIO0: J2.2 (SWDIO), U3.15 (PD1)
/SWDIO1: J3.2 (SWDIO), U4.15 (PD1)
/TX0: J2.6 (SWO), U3.20 (PD6)
/TX1: J3.6 (SWO), U4.20 (PD6)
GND: BZ1.2 (-), C1.2, C2.2, C3.2, C4.2, C5.1, C8.2, C9.1, C13.2, C14.2, C15.2, C16.2, D1.1 (K), D2.1 (K), D3.1 (K), D4.1 (K), J1.A1 (GND), J1.A12 (GND), J1.B1 (GND), J1.B12 (GND), J1.S1 (SHIELD), J2.5 (GND), J3.5 (GND), R1.2, R2.2, U1.3 (AISEN), U1.6 (BISEN), U1.13 (GND), U1.17 (GND), U2.3 (AISEN), U2.6 (BISEN), U2.13 (GND), U2.17 (GND), U3.4 (VSS), U3.21 (VSS), U4.4 (VSS), U4.21 (VSS)
unnamed: D1.2 (A), R3.2
unnamed: D2.2 (A), R4.2
unnamed: D3.2 (A), R5.2
unnamed: D4.2 (A), R6.2
unnamed: L1.1, U1.4 (AOUT2), U1.5 (BOUT2)
unnamed: C6.2, U1.11 (VCP)
unnamed: C5.2, U1.14 (VINT)
unnamed: L2.1, U2.4 (AOUT2)
unnamed: L3.1, U2.5 (BOUT2)
unnamed: C10.2, U2.11 (VCP)
unnamed: C9.2, U2.14 (VINT)
VDD: C1.1, C2.1, F1.1, J1.A4 (VBUS), J1.A9 (VBUS), J1.B4 (VBUS), J1.B9 (VBUS)

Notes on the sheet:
MCU0
DECORATION & LEDS
USB POWER
SMD0805B050TF - 500mA hold, 1A trip - C269104 SMD0805B075TF - 750mA hold, 1.5A trip - C269105
CAPACITIVE TOUCH
MCU1 BUZZER TIM1_RM=01 BUZZ PD2 - T2CH3
MCU0 GUARD TIM1_RM=00 G1 PD3 - T2CH2 G2 PC0 - T2CH3
MCU0 Phases TIM1_RM=11 A1 PC4 - T1CH1 B2 PC7 - T1CH2 A2 PC5 - T1CH3 B1 PD4 - T1CH4
Decoration mounting holes
TOOLING HOLES
MCU1
Assume 2.2V Vd (5.0-2.2)/180 = 16 mA at 100% duty cycle
PHASE DRIVERS
MCU1 LEDS TIM1_RM=11 LED1 PC4 - T1CH1 LED3 PC7 - T1CH2 LED2 PC5 - T1CH3 LED4 PD4 - T1CH4

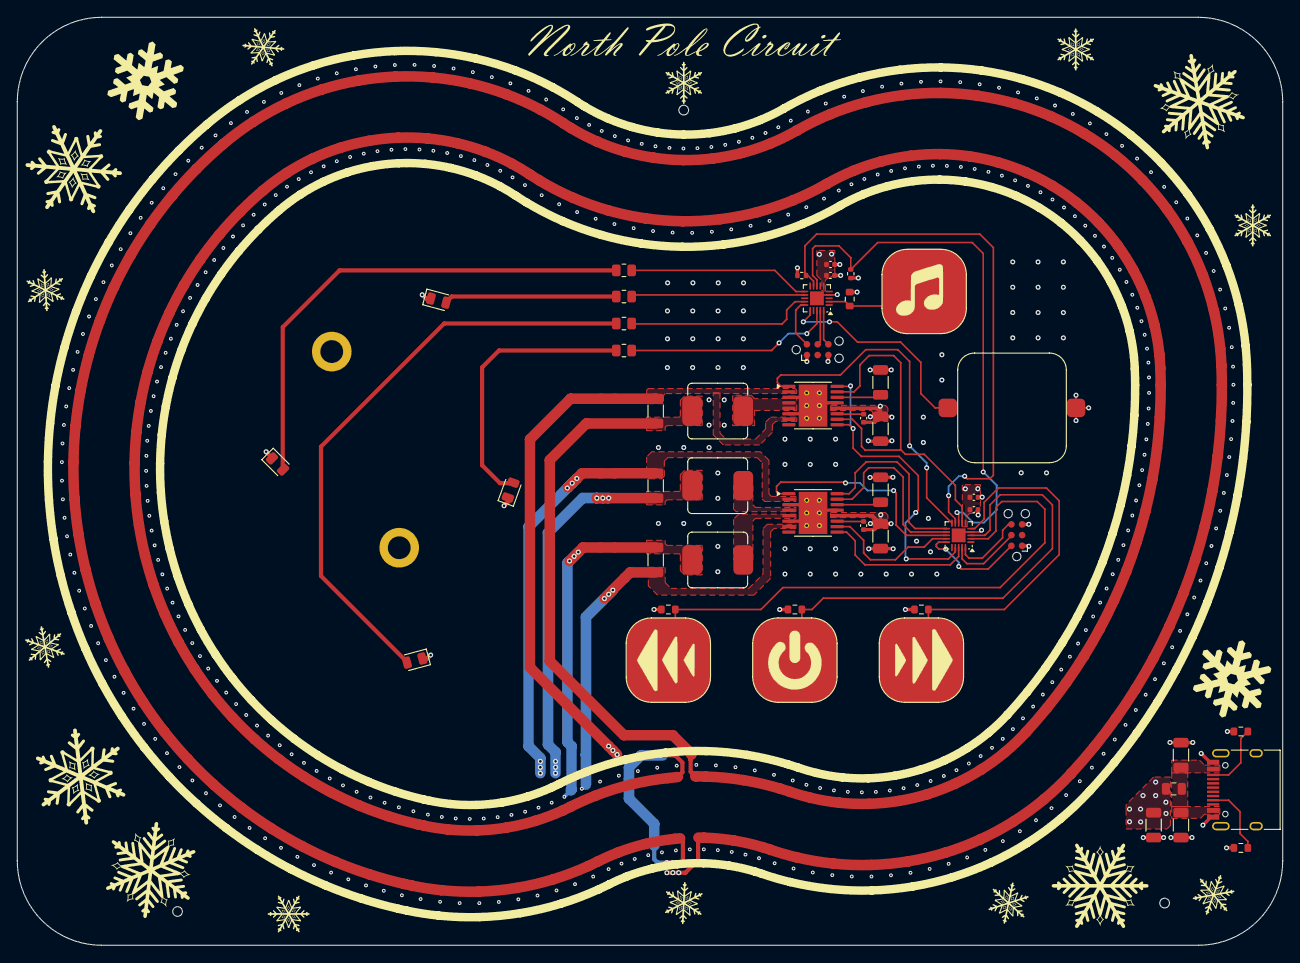
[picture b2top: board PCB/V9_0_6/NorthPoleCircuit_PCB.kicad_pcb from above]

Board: 4 copper layers, 150.0 x 110.0 mm, 56 parts (0 on the bottom side), 47 nets.

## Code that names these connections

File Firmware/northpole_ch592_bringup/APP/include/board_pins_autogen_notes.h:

/* Auto-generated by Firmware/tools/extract_kicad_pinmap.py. */
/* Do not edit by hand; rerun the extractor after KiCad changes. */
#ifndef BOARD_PINS_AUTOGEN_NOTES_H
#define BOARD_PINS_AUTOGEN_NOTES_H

#define BOARD_AUTOGEN_PCB_SHA256 "80ec7a54917bd0ee"
#define BOARD_AUTOGEN_SCH_SHA256 "a72fa80a1a631e47"
#define BOARD_AUTOGEN_AUDIO_UART_CONNECTED 1
#define BOARD_AUTOGEN_AUDIO_HW_BLOCKED 0
#define BOARD_AUTOGEN_RGB_LED_COUNT 6

#define BOARD_U2_PAD_1_FUNCTION "TMR1_1"
#define BOARD_U2_PAD_1_NET "/PWM_A2"
#define BOARD_U2_PAD_1_PINTYPE "bidirectional"
#define BOARD_U2_PAD_2_FUNCTION "PB6_2"
#define BOARD_U2_PAD_2_NET "/HALL1"
#define BOARD_U2_PAD_2_PINTYPE "bidirectional"
#define BOARD_U2_PAD_3_FUNCTION "PB0_3"
#define BOARD_U2_PAD_3_NET "/SLEEP"
#define BOARD_U2_PAD_3_PINTYPE "bidirectional"
#define BOARD_U2_PAD_4_FUNCTION "VDCID_4"
#define BOARD_U2_PAD_4_NET "Net-(U2-VDCIA)"
#define BOARD_U2_PAD_4_PINTYPE "passive"
#define BOARD_U2_PAD_5_FUNCTION "VSW_5"
#define BOARD_U2_PAD_5_NET "Net-(U2-VSW)"
#define BOARD_U2_PAD_5_PINTYPE "passive"
#define BOARD_U2_PAD_6_FUNCTION "VDD33/VIO33_6"
#define BOARD_U2_PAD_6_NET "+3.3V"
#define BOARD_U2_PAD_6_PINTYPE "power_in"
#define BOARD_U2_PAD_7_FUNCTION "AIN10_7"
#define BOARD_U2_PAD_7_NET "/SPD--"
#define BOARD_U2_PAD_7_PINTYPE "input"
#define BOARD_U2_PAD_8_FUNCTION "AIN11_8"
#define BOARD_U2_PAD_8_NET "/RUN"
#define BOARD_U2_PAD_8_PINTYPE "input"
#define BOARD_U2_PAD_9_FUNCTION "AIN12_9"
#define BOARD_U2_PAD_9_NET "/SPD++"
#define BOARD_U2_PAD_9_PINTYPE "input"
#define BOARD_U2_PAD_10_FUNCTION "PA9_10"
#define BOARD_U2_PAD_10_NET "/INT"
#define BOARD_U2_PAD_10_PINTYPE "bidirectional"
#define BOARD_U2_PAD_11_FUNCTION "SCL_11"
#define BOARD_U2_PAD_11_NET "/SWDCK"
#define BOARD_U2_PAD_11_PINTYPE "bidirectional"
#define BOARD_U2_PAD_12_FUNCTION "SDA_12"
#define BOARD_U2_PAD_12_NET "/SWDIO"
#define BOARD_U2_PAD_12_PINTYPE "bidirectional"
#define BOARD_U2_PAD_13_FUNCTION "TXD1__13"
#define BOARD_U2_PAD_13_NET "Net-(U2-PB13)"
#define BOARD_U2_PAD_13_PINTYPE "output"
#define BOARD_U2_PAD_14_FUNCTION "RXD1__14"
#define BOARD_U2_PAD_14_NET "Net-(U2-PB12)"
#define BOARD_U2_PAD_14_PINTYPE "input"
#define BOARD_U2_PAD_15_FUNCTION "UD+_15"
#define BOARD_U2_PAD_15_NET "/DP"
#define BOARD_U2_PAD_15_PINTYPE "bidirectional"
#define BOARD_U2_PAD_16_FUNCTION "UD-_16"
#define BOARD_U2_PAD_16_NET "/DN"
#define BOARD_U2_PAD_16_PINTYPE "bidirectional"
#define BOARD_U2_PAD_17_FUNCTION "PWM9_17"
#define BOARD_U2_PAD_17_NET "/PWM_B1"
#define BOARD_U2_PAD_17_PINTYPE "output"
#define BOARD_U2_PAD_18_FUNCTION "PWM7_18"
#define BOARD_U2_PAD_18_NET "/PWM_B2"
#define BOARD_U2_PAD_18_PINTYPE "output"
#define BOARD_U2_PAD_19_FUNCTION "RST_19"
#define BOARD_U2_PAD_19_NET "Net-(U2-PB23)"
#define BOARD_U2_PAD_19_PINTYPE "bidirectional"
#define BOARD_U2_PAD_20_FUNCTION "PB22_20"
#define BOARD_U2_PAD_20_NET "Net-(U2-PB22)"
#define BOARD_U2_PAD_20_PINTYPE "bidirectional"
#define BOARD_U2_PAD_21_FUNCTION "~{X32MO}_21"
#define BOARD_U2_PAD_21_NET "Net-(U2-~{X32MO})"
#define BOARD_U2_PAD_21_PINTYPE "output"
#define BOARD_U2_PAD_22_FUNCTION "X32MI_22"
#define BOARD_U2_PAD_22_NET "Net-(U2-X32MI)"
#define BOARD_U2_PAD_22_PINTYPE "input"
#define BOARD_U2_PAD_23_FUNCTION "VINTA_23"
#define BOARD_U2_PAD_23_NET "Net-(U2-VINTA)"
#define BOARD_U2_PAD_23_PINTYPE "passive"
#define BOARD_U2_PAD_24_FUNCTION "ANT_24"
#define BOARD_U2_PAD_24_NET "Net-(AE1-A)"
#define BOARD_U2_PAD_24_PINTYPE "bidirectional"
#define BOARD_U2_PAD_25_FUNCTION "VDCIA_25"
#define BOARD_U2_PAD_25_NET "Net-(U2-VDCIA)"
#define BOARD_U2_PAD_25_PINTYPE "passive"
#define BOARD_U2_PAD_26_FUNCTION "PA4_26"
#define BOARD_U2_PAD_26_NET "/HALL2"
#define BOARD_U2_PAD_26_PINTYPE "bidirectional"
#define BOARD_U2_PAD_27_FUNCTION "AIN1_27"
#define BOARD_U2_PAD_27_NET "/MUSIC"
#define BOARD_U2_PAD_27_PINTYPE "input"
#define BOARD_U2_PAD_28_FUNCTION "PA15_28"
#define BOARD_U2_PAD_28_NET "/LED"
#define BOARD_U2_PAD_28_PINTYPE "bidirectional"
#define BOARD_U2_PAD_29_FUNCTION "PA14_29"
#define BOARD_U2_PAD_29_NET "/BUSY"
#define BOARD_U2_PAD_29_PINTYPE "bidirectional"
#define BOARD_U2_PAD_30_FUNCTION "PWM5_30"
#define BOARD_U2_PAD_30_NET "/PWM_G1"
#define BOARD_U2_PAD_30_PINTYPE "output"
#define BOARD_U2_PAD_31_FUNCTION "PWM4_31"
#define BOARD_U2_PAD_31_NET "/PWM_G2"
#define BOARD_U2_PAD_31_PINTYPE "output"
#define BOARD_U2_PAD_32_FUNCTION "TMR2_32"
#define BOARD_U2_PAD_32_NET "/PWM_A1"
#define BOARD_U2_PAD_32_PINTYPE "bidirectional"
#define BOARD_U2_PAD_33_FUNCTION "GND_33"
#define BOARD_U2_PAD_33_NET "GND"
#define BOARD_U2_PAD_33_PINTYPE "power_in"

#endif /* BOARD_PINS_AUTOGEN_NOTES_H */

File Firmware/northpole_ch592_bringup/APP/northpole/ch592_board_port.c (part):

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
    switch (pin->u2_pad) {
    case 1: hw->port = HW_PORT_A; hw->mask = bTMR1; break;       /* /PWM_A2 */
    case 2: hw->port = HW_PORT_B; hw->mask = GPIO_Pin_6; break;  /* /HALL1 */
    case 3: hw->port = HW_PORT_B; hw->mask = GPIO_Pin_0; break;  /* /SLEEP */
    case 7: hw->port = HW_PORT_A; hw->mask = bAIN10; break;      /* /SPD-- */
    case 8: hw->port = HW_PORT_A; hw->mask = bAIN11; break;      /* /RUN */
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    case 14: hw->port = HW_PORT_B; hw->mask = bRXD1_; break;     /* WT TX */
    case 17: hw->port = HW_PORT_B; hw->mask = bPWM9; break;      /* /PWM_B1 */
    case 18: hw->port = HW_PORT_B; hw->mask = bPWM7; break;      /* /PWM_B2 */
    case 26: hw->port = HW_PORT_A; hw->mask = GPIO_Pin_4; break; /* /HALL2 */
    case 27: hw->port = HW_PORT_A; hw->mask = bAIN1; break;      /* /MUSIC */
    case 28: hw->port = HW_PORT_A; hw->mask = GPIO_Pin_15; break;/* /LED */
    case 29: hw->port = HW_PORT_A; hw->mask = GPIO_Pin_14; break;/* /BUSY */
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    }
    motor_pwm_platform_initialized = 1u;

    GPIOPinRemap(DISABLE, RB_PIN_TMR1); /* PA10/TMR1 is /PWM_A2 on this PCB. */
    GPIOPinRemap(DISABLE, RB_PIN_TMR2); /* PA11/TMR2 is /PWM_A1 on this PCB. */

    TMR1_PWMCycleCfg(motor_timer_cycle_ticks);
    TMR1_PWMInit(High_Level, PWM_Times_1);
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    motor_pwmx_disable_low(CH_PWM4, (hw_pin_t){HW_PORT_A, bPWM4});

#if APP_MOTOR_PWM_BACKEND_ENABLE
    GPIOPinRemap(DISABLE, RB_PIN_TMR1); /* PA10/TMR1 is /PWM_A2 on this PCB. */
    GPIOPinRemap(DISABLE, RB_PIN_TMR2); /* PA11/TMR2 is /PWM_A1 on this PCB. */

    TMR1_PWMCycleCfg(motor_timer_cycle_ticks);
    TMR1_PWMActDataWidth(0);
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const char *rgb_ws2812_platform_backend_name(void)
{
#if APP_RGB_WS2812_USE_SPI0_MOSI_PA14
    return "spi0-mosi-pa14";
#elif APP_RGB_WS2812_USE_PA14_BITBANG
    return "bitbang-pa14";
#else
    return "bitbang-pa15";
#endif
}

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
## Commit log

2026-05-05 Add BLE audio card hardware revision
2026-05-09 Schematics and PCB update. Fiirmware v0.1
2026-05-18 Final PCB update before ordering. Firmware update based on the CH592 Dev Board.
2026-06-05 First tests on real PCB. PCB is alive. FW comfirms most of the functionality including BLE. Hall sensor has footprint bug. IP5209 chip still not charging the battery. LED is producing only WHITE.
2026-06-09 First FW which moves the sledge. LED issue is fixed. Proper scope readouts
2026-06-13 First MVP FW which integrates all the functionality. Motion still works but not that well with other parts like Music, LEDs, Halls and Touch.
